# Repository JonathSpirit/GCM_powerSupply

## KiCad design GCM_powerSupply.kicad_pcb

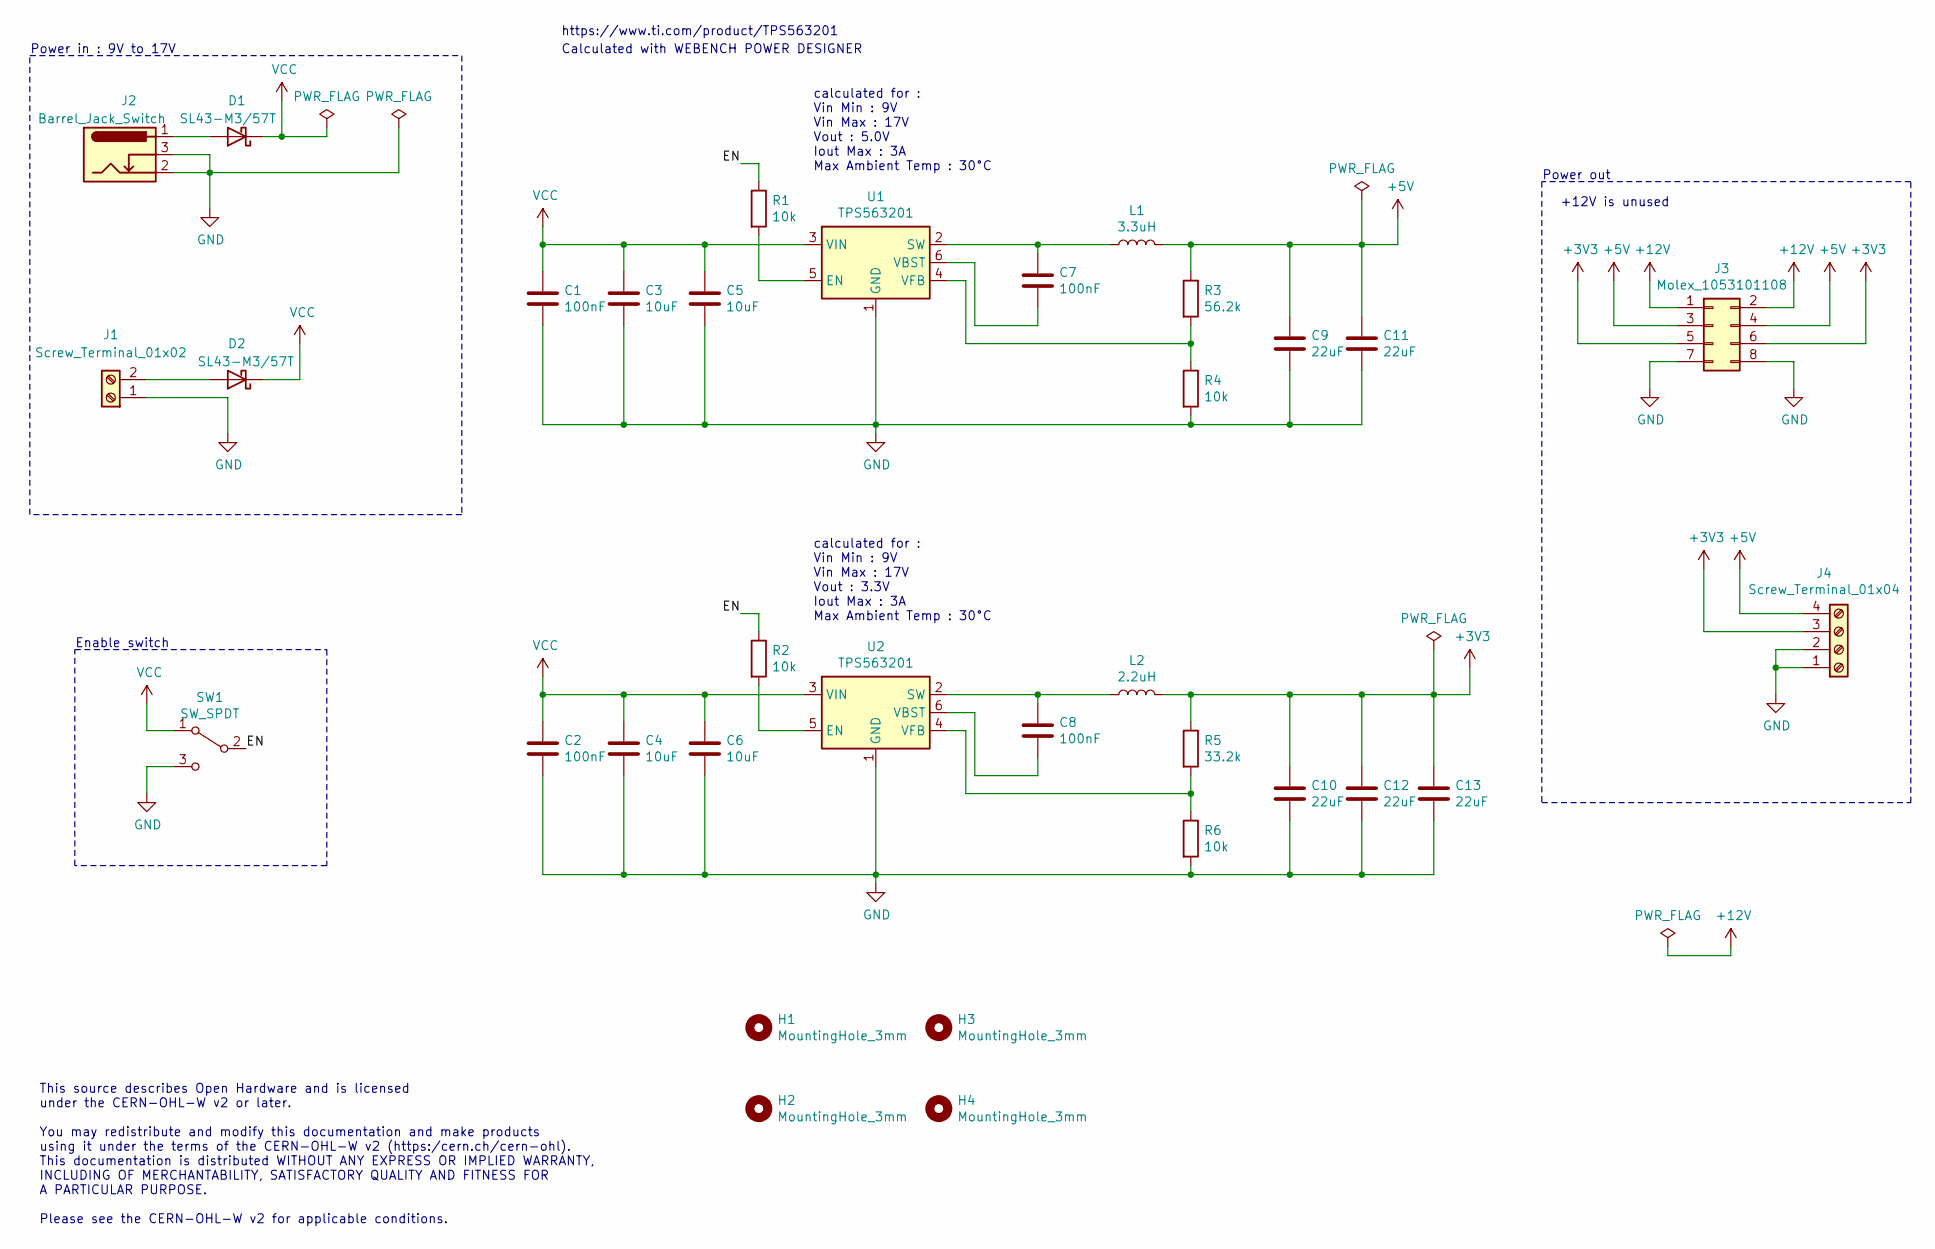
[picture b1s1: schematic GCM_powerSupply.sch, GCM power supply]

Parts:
C1, C2, C7, C8: 100nF; C_1206_3216Metric
C3, C4, C5, C6: 10uF; C_1206_3216Metric
C9, C10, C11, C12, C13: 22uF; C_1206_3216Metric
D1, D2: SL43-M3/57T; D_SMC
H1, H2, H3, H4: MountingHole_3mm
J1: Screw_Terminal_01x02; TerminalBlock_Phoenix_MPT-0,5-2-2.54_1x02_P2.54mm_Horizontal
J2: Barrel_Jack_Switch; BarrelJack_Horizontal
J3: Molex_1053101108; Molex_Nano-Fit_105310-xx08_2x04_P2.50mm_Vertical
J4: Screw_Terminal_01x04; TerminalBlock_Phoenix_MPT-0,5-4-2.54_1x04_P2.54mm_Horizontal
L1: 3.3uH; PQ2614BLA
L2: 2.2uH; PQ2614BLA
R1, R2, R4, R6: 10k; R_0805_2012Metric
R3: 56.2k; R_0805_2012Metric
R5: 33.2k; R_0805_2012Metric
SW1: SW_SPDT; EG1218
U1, U2: TPS563201; SOT-23-6

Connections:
+3V3: C10.1, C12.1, C13.1, J3.5, J3.6, J4.3, L2.2, R5.1
+5V: C9.1, C11.1, J3.3, J3.4, J4.4, L1.2, R3.1
+12V: J3.1, J3.2
/EN: R1.1, R2.1, SW1.2 (B)
GND: C1.2, C2.2, C3.2, C4.2, C5.2, C6.2, C9.2, C10.2, C11.2, C12.2, C13.2, J1.1, J2.2, J2.3, J3.7, J3.8, J4.1, J4.2, R4.2, R6.2, SW1.3 (C), U1.1 (GND), U2.1 (GND)
unnamed: C7.1, L1.1, U1.2 (SW)
unnamed: C7.2, U1.6 (VBST)
unnamed: C8.1, L2.1, U2.2 (SW)
unnamed: C8.2, U2.6 (VBST)
unnamed: D1.2 (A), J2.1
unnamed: D2.2 (A), J1.2
unnamed: R1.2, U1.5 (EN)
unnamed: R2.2, U2.5 (EN)
unnamed: R3.2, R4.1, U1.4 (VFB)
unnamed: R5.2, R6.1, U2.4 (VFB)
VCC: C1.1, C2.1, C3.1, C4.1, C5.1, C6.1, D1.1 (K), D2.1 (K), SW1.1 (A), U1.3 (VIN), U2.3 (VIN)

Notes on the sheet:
This source describes Open Hardware and is licensed under the CERN-OHL-W v2 or later. You may redistribute and modify this documentation and make products using it under the terms of the CERN-OHL-W v2 (https:/cern.ch/cern-ohl). This documentation is distributed WITHOUT ANY EXPRESS OR IMPLIED WARRAN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
+12V is unused
https://www.ti.com/product/TPS563201
Power in : 9V to 17V
calculated for : Vin Min : 9V Vin Max : 17V Vout : 5.0V Iout Max : 3A Max Ambient Temp : 30°C
calculated for : Vin Min : 9V Vin Max : 17V Vout : 3.3V Iout Max : 3A Max Ambient Temp : 30°C
Calculated with WEBENCH POWER DESIGNER
Enable switch
Power out

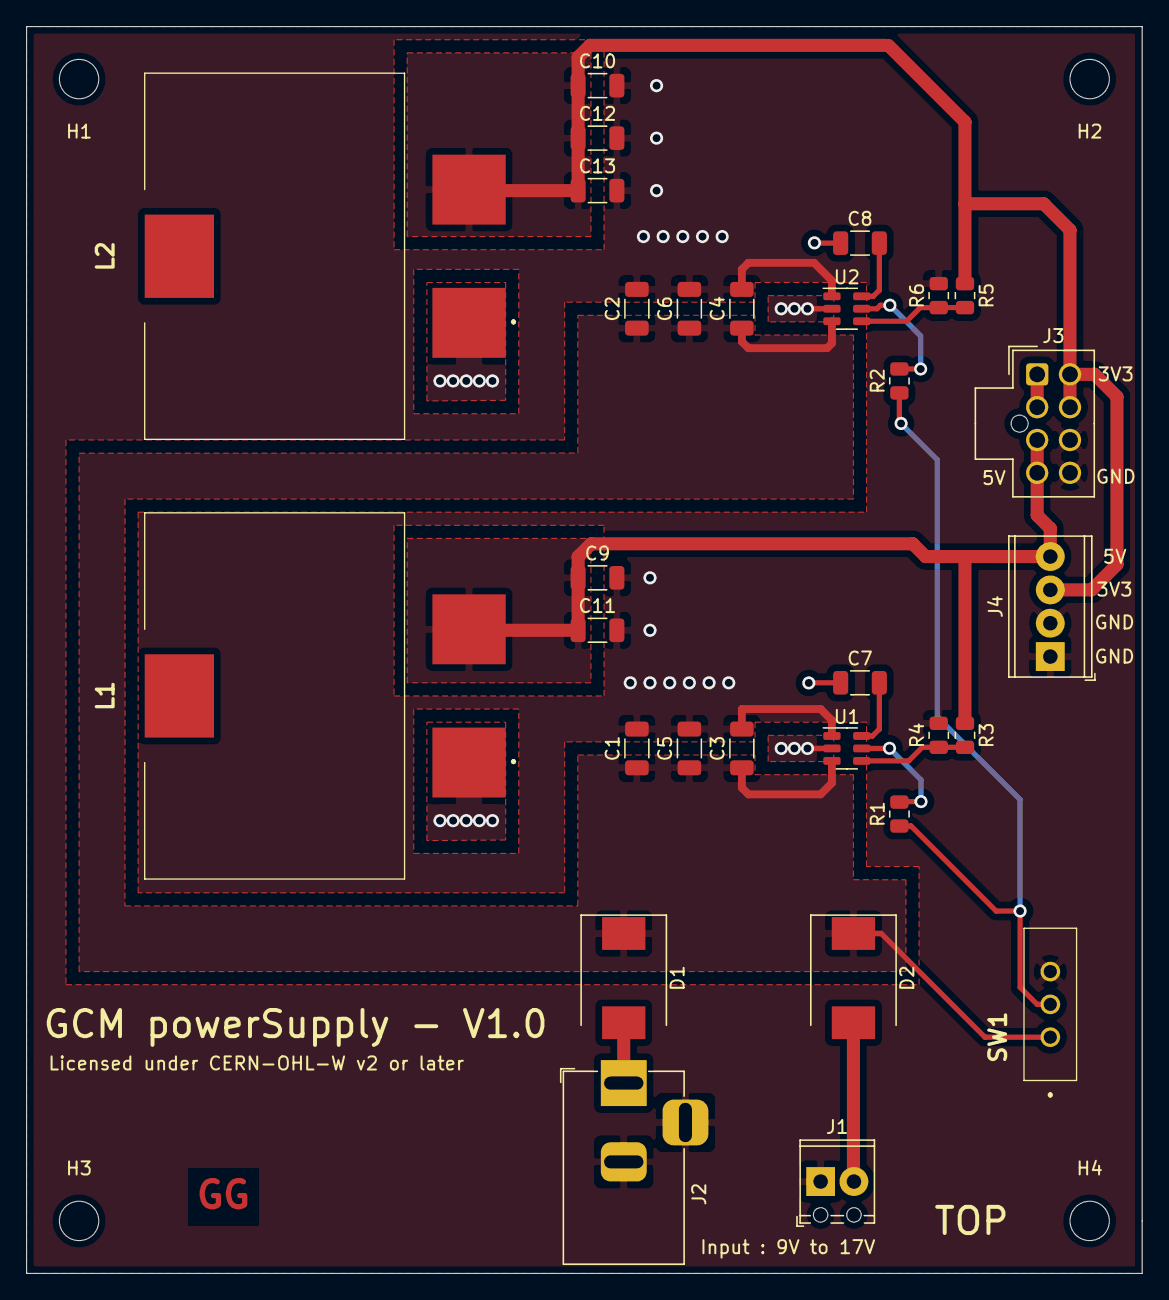
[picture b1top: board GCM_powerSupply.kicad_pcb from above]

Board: 2 copper layers, 85.0 x 95.0 mm, 34 parts (0 on the bottom side), 16 nets.

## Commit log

2021-03-29 Add gitignore
2021-03-29 Initial push
2021-03-29 Fix R0805 was 1206, change the switch
2021-03-29 Larger thermal brake

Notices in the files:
GCM_powerSupply.kicad_pcb:
Copyright Guillaume Guillet 2021
Licensed under CERN-OHL-W v2 or later
